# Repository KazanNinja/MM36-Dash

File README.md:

Main code for the dash of CSUN Matador Motorsport's 2024-2025 vehicle. Blah blah blah more writing soon.

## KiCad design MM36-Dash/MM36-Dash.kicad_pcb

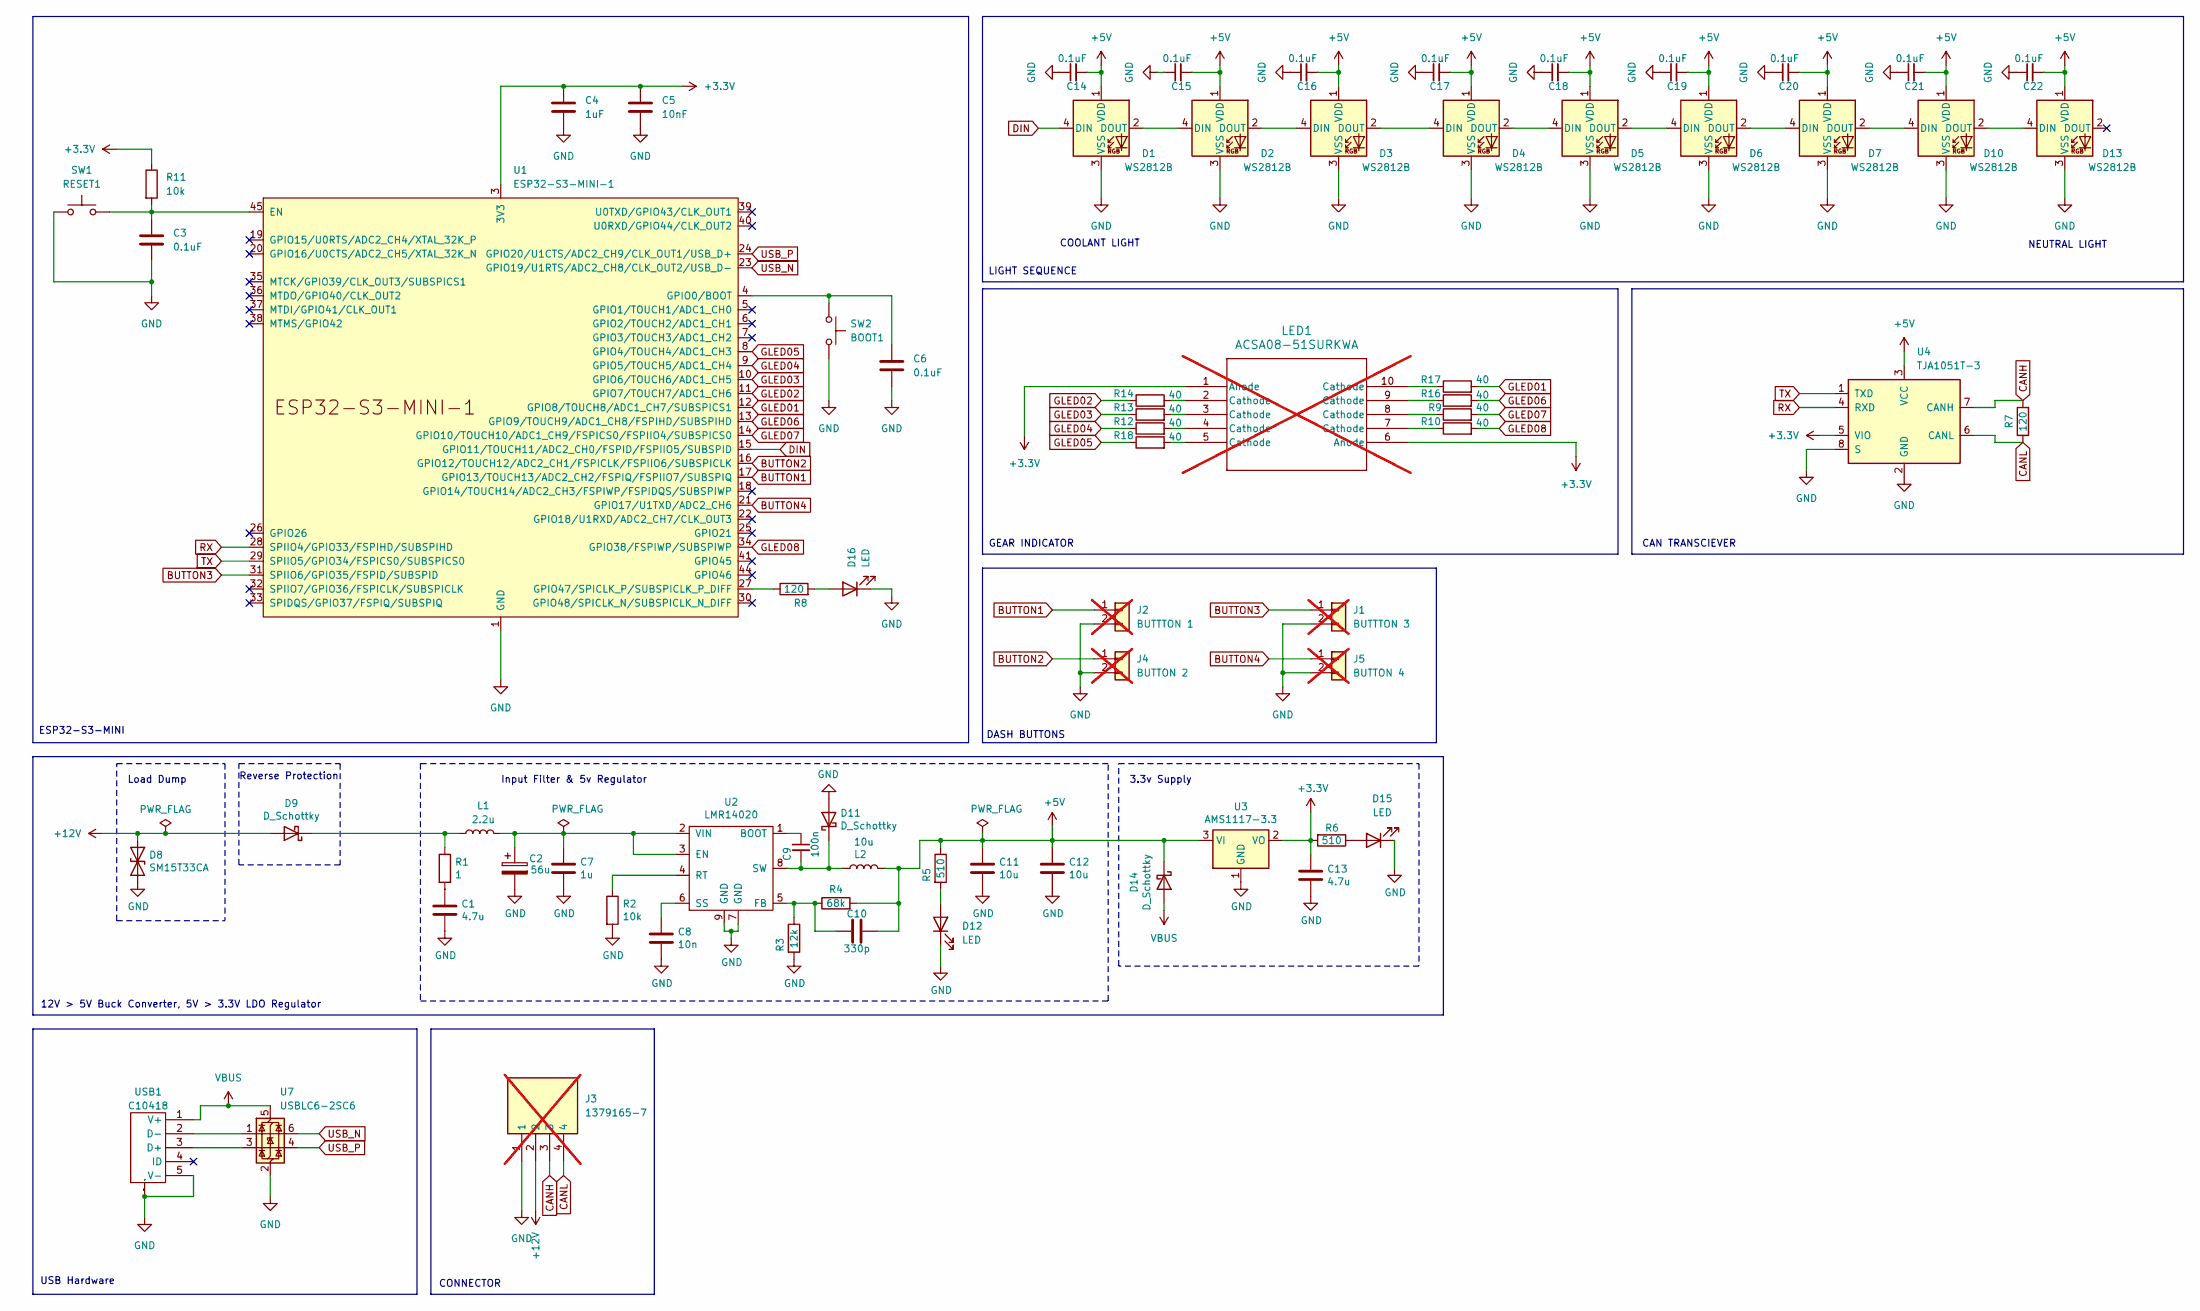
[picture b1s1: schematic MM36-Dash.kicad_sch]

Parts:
C1, C13: 4.7u; C_0603_1608Metric; LCSC C19666
C2: 56u; CP_Radial_D8.0mm_P2.50mm; LCSC C106629
C3, C6, C14, C15, C16, C17, C18, C19, C20, C21, C22: 0.1uF; C_0603_1608Metric; LCSC C14663
C4: 1uF; C_0603_1608Metric; LCSC C15849
C5: 10nF; C_0603_1608Metric; LCSC C57112
C7: 1u; C_0603_1608Metric; LCSC C15849
C8: 10n; C_0603_1608Metric; LCSC C57112
C9: 100n; C_0603_1608Metric; LCSC C14663
C10: 330p; C_0603_1608Metric; LCSC C1664
C11, C12: 10u; C_1206_3216Metric; LCSC C13585
D1, D2, D3, D4, D5, D6, D7, D10, D13: WS2812B; LED_WS2812B_PLCC4_5.0x5.0mm_P3.2mm; LCSC C2761795
D8: SM15T33CA; D_SMC; LCSC C151281
D9, D11, D14: D_Schottky; D_SMA; LCSC C8678
D12, D15, D16: LED; LED_0805_2012Metric; JLCPCB C2297
J1: BUTTTON 3; PinSocket_1x02_P1.27mm_Vertical; not fitted
J2: BUTTTON 1; PinSocket_1x02_P1.27mm_Vertical; not fitted
J3: 1379165-7; 13791657; Manufacturer_Part_Number 1379165-7; Mouser Part Number 571-1379165-7; not fitted
J4: BUTTON 2; PinSocket_1x02_P1.27mm_Vertical; not fitted
J5: BUTTON 4; PinSocket_1x02_P1.27mm_Vertical; not fitted
L1: 2.2u; L_1210_3225Metric; LCSC C286757
L2: 10u; L_Sunlord_MWSA0503S; LCSC C408412
LED1: ACSA08-51SURKWA; LED10_ACSA08-51SURKWA_KNB; not fitted
R1: 1; R_0603_1608Metric; LCSC C22936
R2, R11: 10k; R_0603_1608Metric; LCSC C25804
R3: 12k; R_0603_1608Metric; LCSC C22790
R4: 68k; R_0603_1608Metric; LCSC C23231
R5, R6: 510; R_0603_1608Metric; LCSC C23193
R7, R8: 120; R_0603_1608Metric; LCSC C22787
R9, R10, R12, R13, R14, R16, R17, R18: 40; R_0805_2012Metric; LCSC C5355206
SW1: RESET1; SW_SPST_TL3342; LCSC C318884
SW2: BOOT1; SW_SPST_TL3342; LCSC C318884
U1: ESP32-S3-MINI-1; ESP32-S3-MINI-1U; LCSC C2980299
U2: LMR14020; SOIC-8-1EP_3.9x4.9mm_P1.27mm_EP2.29x3mm; LCSC C187824
U3: AMS1117-3.3; SOT-223-3_TabPin2; LCSC C6186
U4: TJA1051T-3; SOIC-8_3.9x4.9mm_P1.27mm; LCSC C5342108
U7: USBLC6-2SC6; SOT-23-6; LCSC C2827654
USB1: C10418; MICRO-USB-SMD_5P-P0.65-H-F_C10418; Manufacturer Part 920-E52A2021S10100; LCSC Part Name Micro-B 母

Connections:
+3.3V: C4.1, C5.1, C13.1, LED1.1 (Anode), LED1.6 (Anode), R6.2, R11.1, U1.3 (3V3), U3.2 (VO), U4.5 (VIO)
+5V: C10.1, C11.1, C12.1, C14.2, C15.2, C16.2, C17.2, C18.2, C19.2, C20.2, C21.2, C22.2, D1.1 (VDD), D2.1 (VDD), D3.1 (VDD), D4.1 (VDD), D5.1 (VDD), D6.1 (VDD), D7.1 (VDD), D10.1 (VDD), D13.1 (VDD), D14.1 (K), L2.2, R4.2, R5.1, U3.3 (VI), U4.3 (VCC)
+12V: D8.1 (A1), D9.2 (A), J3.2
BUTTON1: J2.1, U1.17 (GPIO13/TOUCH13/ADC2_CH2/FSPIQ/FSPIIO7/S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)
BUTTON2: J4.1, U1.16 (GPIO12/TOUCH12/ADC2_CH1/FSPICLK/FSPIIO6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)
BUTTON3: J1.1, U1.31 (SPIIO6/GPIO35/FSPID/SUBSPID)
BUTTON4: J5.1, U1.21 (GPIO17/U1TXD/ADC2_CH6)
CANH: J3.3, R7.2, U4.7 (CANH)
CANL: J3.4, R7.1, U4.6 (CANL)
DIN: D1.4 (DIN), U1.15 (GPIO11/TOUCH11/ADC2_CH0/FSPID/FSPIIO5/S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)
GLED01: R17.2, U1.12 (GPIO8/TOUCH8/ADC1_CH7/SUBSPICS1)
GLED02: R14.1, U1.11 (GPIO7/TOUCH7/ADC1_CH6)
GLED03: R13.1, U1.10 (GPIO6/TOUCH6/ADC1_CH5)
GLED04: R12.1, U1.9 (GPIO5/TOUCH5/ADC1_CH4)
GLED05: R18.1, U1.8 (GPIO4/TOUCH4/ADC1_CH3)
GLED06: R16.2, U1.13 (GPIO9/TOUCH9/ADC1_CH8/FSPIHD/SUBSPIHD)
GLED07: R9.2, U1.14 (GPIO10/TOUCH10/ADC1_CH9/FSPICS0/FSPIIO4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)
GLED08: R10.2, U1.34 (GPIO38/FSPIWP/SUBSPIWP)
GND: C1.2, C2.2, C3.2, C4.2, C5.2, C6.2, C7.2, C8.2, C11.2, C12.2, C13.2, C14.1, C15.1, C16.1, C17.1, C18.1, C19.1, C20.1, C21.1, C22.1, D1.3 (VSS), D2.3 (VSS), D3.3 (VSS), D4.3 (VSS), D5.3 (VSS), D6.3 (VSS), D7.3 (VSS), D8.2 (A2), D10.3 (VSS), D11.2 (A), D12.1 (K), D13.3 (VSS), D15.1 (K), D16.1 (K), J1.2, J2.2, J3.1, J4.2, J5.2, R2.2, R3.2, SW1.2, SW2.2, U1.1 (GND), U1.2 (GND), U1.42 (GND), U1.43 (GND), U1.46 (GND), U1.47 (GND), U1.48 (GND), U1.49 (GND), U1.50 (GND), U1.51 (GND), U1.52 (GND), U1.53 (GND), U1.54 (GND), U1.55 (GND), U1.56 (GND), U1.57 (GND), U1.58 (GND), U1.59 (GND), U1.60 (GND), U1.61 (GND), U1.62 (GND), U1.63 (GND), U1.64 (GND), U1.65 (GND), U2.7 (GND), U2.9 (GND), U3.1 (GND), U4.2 (GND), U4.8 (S), U7.2 (GND), USB1.5 (V-), USB1.SH0 (MTN), USB1.SH1 (1), USB1.SH2 (2), USB1.SH3 (3); also elsewhere on the board
unnamed: C1.1, R1.2
unnamed: D1.2 (DOUT), D2.4 (DIN)
unnamed: D2.2 (DOUT), D3.4 (DIN)
unnamed: D3.2 (DOUT), D4.4 (DIN)
unnamed: D4.2 (DOUT), D5.4 (DIN)
unnamed: D5.2 (DOUT), D6.4 (DIN)
unnamed: D6.2 (DOUT), D7.4 (DIN)
unnamed: D9.1 (K), L1.1, R1.1
unnamed: D7.2 (DOUT), D10.4 (DIN)
unnamed: D10.2 (DOUT), D13.4 (DIN)
unnamed: C9.2, D11.1 (K), L2.1, U2.8 (SW)
unnamed: D12.2 (A), R5.2
unnamed: D15.2 (A), R6.1
unnamed: D16.2 (A), R8.2
unnamed: LED1.2 (Cathode), R14.2
unnamed: LED1.3 (Cathode), R13.2
unnamed: LED1.4 (Cathode), R12.2
unnamed: LED1.5 (Cathode), R18.2
unnamed: LED1.7 (Cathode), R10.1
unnamed: LED1.8 (Cathode), R9.1
unnamed: LED1.9 (Cathode), R16.1
unnamed: LED1.10 (Cathode), R17.1
unnamed: C3.1, R11.2, SW1.1, U1.45 (EN)
unnamed: C6.1, SW2.1, U1.4 (GPIO0/BOOT)
unnamed: R8.1, U1.27 (GPIO47/SPICLK_P/SUBSPICLK_P_DIFF)
unnamed: C9.1, U2.1 (BOOT)
unnamed: C2.1, C7.1, L1.2, U2.2 (VIN), U2.3 (EN)
unnamed: C10.2, R3.1, R4.1, U2.5 (FB)
unnamed: R2.1, U2.4 (RT)
unnamed: C8.1, U2.6 (SS)
unnamed: U7.3 (I/O2), USB1.3 (D+)
unnamed: U7.1 (I/O1), USB1.2 (D-)
RX: U1.28 (SPIIO4/GPIO33/FSPIHD/SUBSPIHD), U4.4 (RXD)
TX: U1.29 (SPIIO5/GPIO34/FSPICS0/SUBSPICS0), U4.1 (TXD)
USB_N: U1.23 (GPIO19/U1RTS/ADC2_CH8/CLK_OUT2/USB_D-), U7.6 (I/O1)
USB_P: U1.24 (GPIO20/U1CTS/ADC2_CH9/CLK_OUT1/USB_D+), U7.4 (I/O2)
VBUS: D14.2 (A), U7.5 (VBUS), USB1.1 (V+)

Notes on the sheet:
Input Filter & 5v Regulator
DASH BUTTONS
ESP32-S3-MINI
NEUTRAL LIGHT
GEAR INDICATOR
Reverse Protection
CONNECTOR
COOLANT LIGHT
LIGHT SEQUENCE
USB Hardware
CAN TRANSCIEVER
Load Dump
12V > 5V Buck Converter, 5V > 3.3V LDO Regulator
3.3v Supply

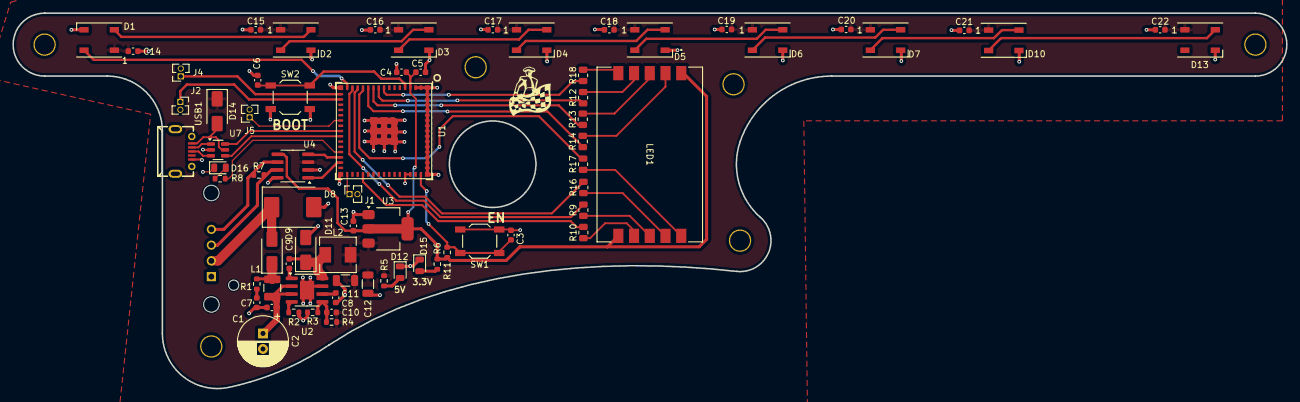
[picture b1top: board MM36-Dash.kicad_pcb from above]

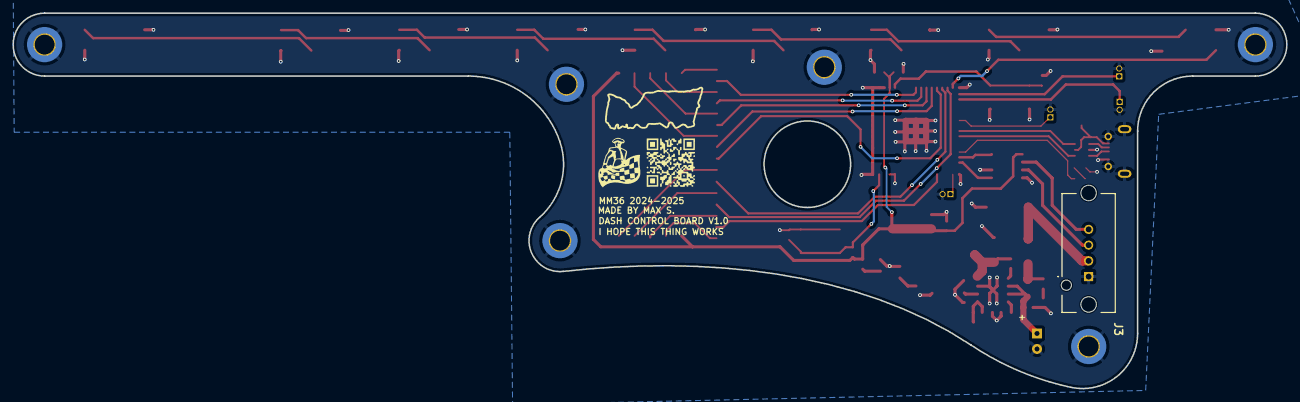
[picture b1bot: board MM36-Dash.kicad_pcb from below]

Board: 2 copper layers, 205.7 x 60.6 mm, 73 parts (3 on the bottom side), 56 nets.

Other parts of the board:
H1, H1#2: MountingHole_3.2mm_M3_ISO7380_Pad_TopOnly

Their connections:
GND: H1.1, H1#2.1; also elsewhere on the board

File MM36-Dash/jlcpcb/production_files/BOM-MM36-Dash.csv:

Comment,Designator,Footprint,LCSC,Quantity
C10418,USB1,MICRO-USB-SMD_5P-P0.65-H-F_C10418,C10418,1
56u,C2,CP_Radial_D8.0mm_P2.50mm,C106629,1
10u,"C11,C12",C_1206_3216Metric,C13585,2
0.1uF,"C14,C15,C16,C17,C18,C19,C20,C21,C22,C3,C6,C9",C_0603_1608Metric,C14663,12
SM15T33CA,D8,D_SMC,C151281,1
1uF,"C4,C7",C_0603_1608Metric,C15849,2
330p,C10,C_0603_1608Metric,C1664,1
LMR14020,U2,SOIC-8-1EP_3.9x4.9mm_P1.27mm_EP2.29x3mm,C187824,1
4.7u,"C1,C13",C_0603_1608Metric,C19666,2
120,"R7,R8",R_0603_1608Metric,C22787,2
12k,R3,R_0603_1608Metric,C22790,1
1,R1,R_0603_1608Metric,C22936,1
LED,"D12,D15,D16",LED_0805_2012Metric,C2297,3
510,"R5,R6",R_0603_1608Metric,C23193,2
68k,R4,R_0603_1608Metric,C23231,1
10k,"R11,R2",R_0603_1608Metric,C25804,2
WS2812B,"D1,D10,D13,D2,D3,D4,D5,D6,D7",LED_WS2812B_PLCC4_5.0x5.0mm_P3.2mm,C2761795,9
USBLC6-2SC6,U7,SOT-23-6,C2827654,1
2.2u,L1,L_1210_3225Metric,C286757,1
ESP32-S3-MINI-1,U1,ESP32-S3-MINI-1U,C2980299,1
RESET1,"SW1,SW2",SW_SPST_TL3342,C318884,2
10u,L2,L_Sunlord_MWSA0503S,C408412,1
TJA1051T-3,U4,SOIC-8_3.9x4.9mm_P1.27mm,C5342108,1
40,"R10,R12,R13,R14,R16,R17,R18,R9",R_0805_2012Metric,C5355206,8
10nF,"C5,C8",C_0603_1608Metric,C57112,2
AMS1117-3.3,U3,SOT-223-3_TabPin2,C6186,1
D_Schottky,"D11,D14,D9",D_SMA,C8678,3

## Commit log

2025-02-04 Update MM36-Dash.ino
    Laying out most of the dongers
2025-02-05 Mo Updates
    MOre stuffz
2025-02-15 Update MM36-Dash.ino
    Dev stuff
2025-02-16 Major Update
    Adding flashing lights, all the shabang big thangz
2025-02-16 Mo Big Stuff
    Some clearning up, some CAN prep
2025-02-16 Gear Positions
    Added gear position things for the segment display
2025-02-16 Cleaned up, more gear position logic
    added timer for gear 14 error code thing
2025-02-16 Status LED Stuff
    Made some changes to status LED
2025-02-16 More status LED
    idk im just messing with stuff now
2025-02-16 CAN Confirmation
    Confirmed CAN TX/RX is working with protoboard. Some clean up of items that were used for testing.
    All is well
2025-02-17 Gear Indicator
    Accidentally flipped 7-segment display in PCB layout, corrected pinouts on ESP for that. Other RTOS priority changes. vTaskDelay changes. 7-segment also pulls HIGH on segments not needed for correspo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
2025-02-18 Converging Shift Lights
    Shift lights changed to converging style
2025-02-18 Added KiCAD Files
2025-02-19 Non-RTOS Version
    Was having issues using RTOS. This branch was made for non-RTOS development in case this proves to work well
2025-02-19 Somethings Happening
    Is it working!?!?
2025-02-20 RTOS and CAN Changes
    Changes in task core pinning, priority, and stack sizees. CAN got larger queue sizes
2025-02-20 Latest Revision
    Corrected RPM thresholds, removed print statement
2025-03-11 RTOS
    Changed some RTOS stuff so the main tasks run at fixed intervals and not just ass blasting all the time
2025-04-14 Bare Metal
    Bare metal cause I can, fully functional and probably one of the final iterations
